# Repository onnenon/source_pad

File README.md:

# Source Pad

The Source Allies logo looks too similar to a 3x3 macropad to not make it into one...

## Case

## Source Code

## PCB

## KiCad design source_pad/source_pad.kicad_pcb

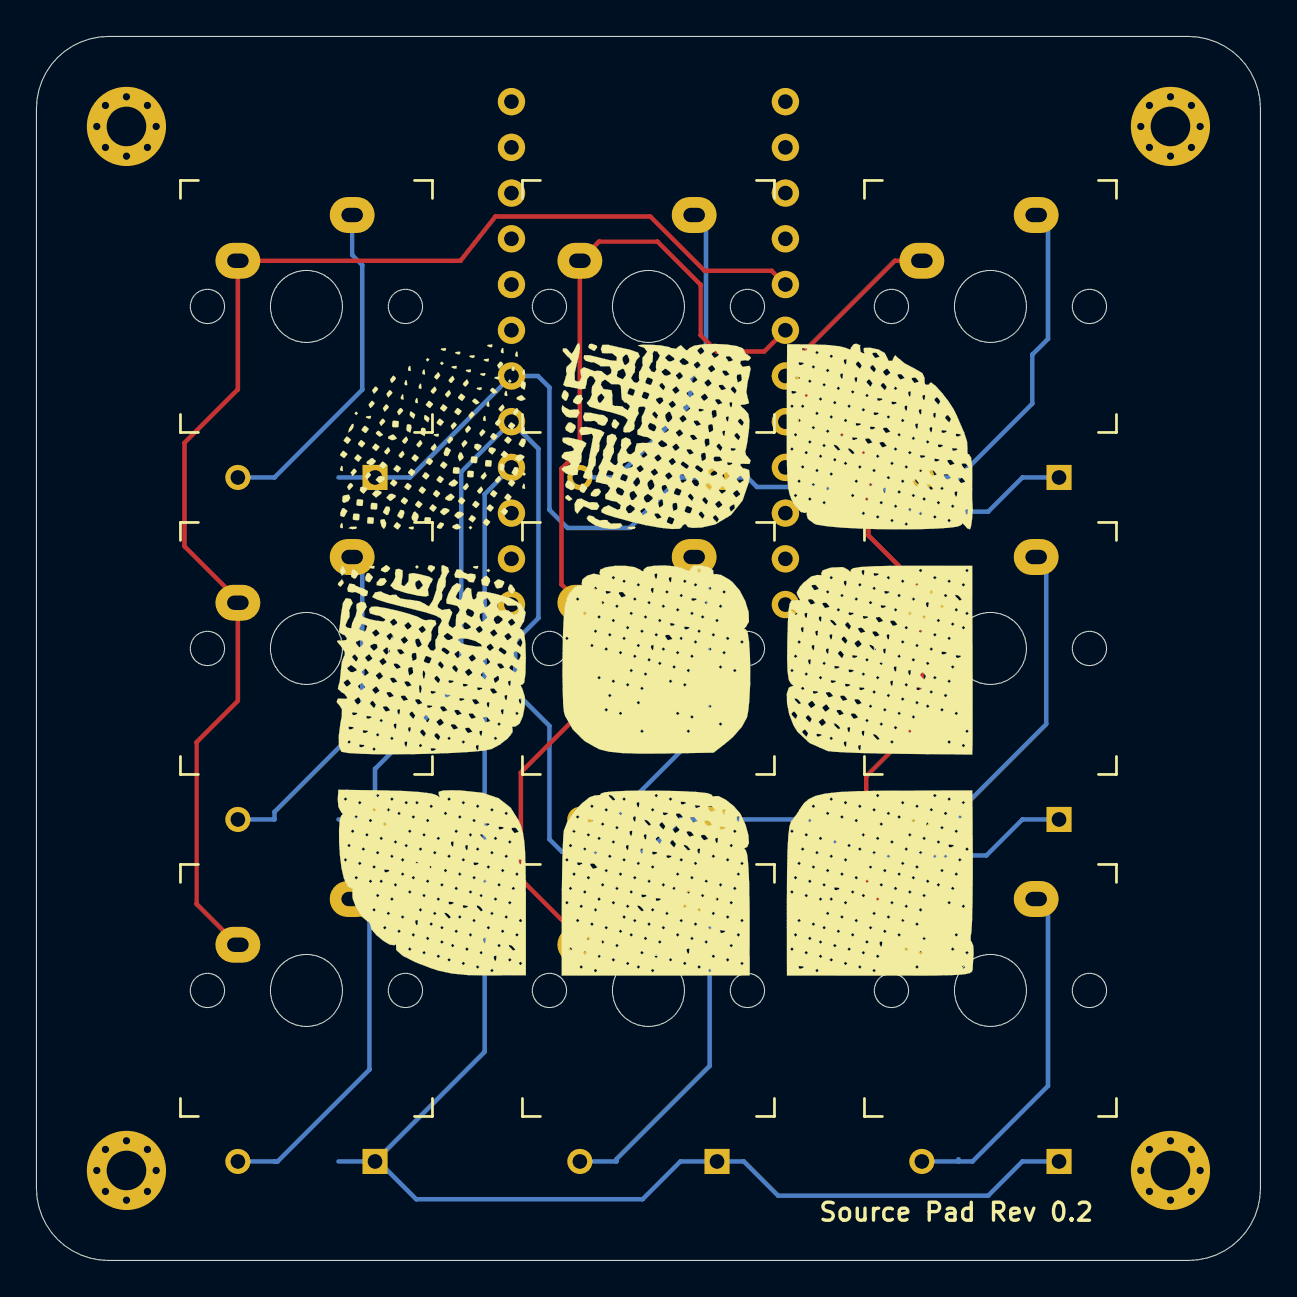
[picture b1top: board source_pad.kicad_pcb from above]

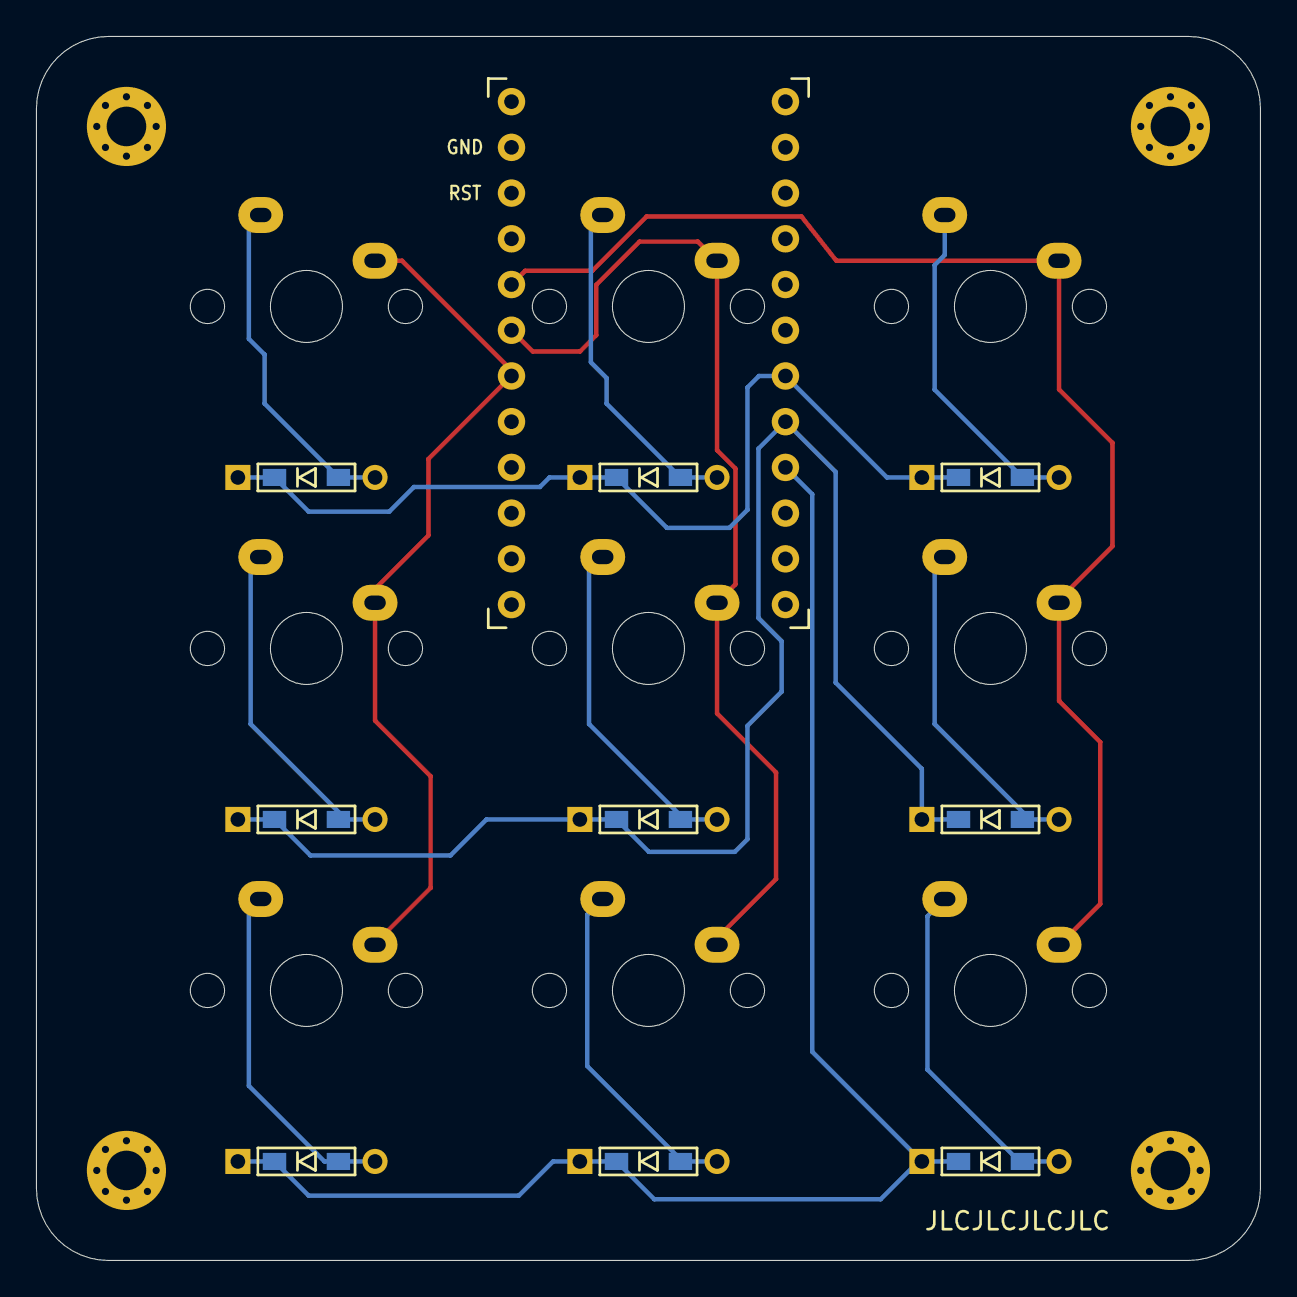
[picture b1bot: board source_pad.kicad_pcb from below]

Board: 2 copper layers, 68.0 x 68.0 mm, 19 parts (10 on the bottom side), 15 nets.

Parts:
D1, D2, D3, D4, D5, D6, D7, D8, D9: 1N4148W; D3_TH_SMD_SINGLE_SIDE
SW1, SW2, SW3, SW4, SW5, SW6, SW7, SW8, SW9: SW_PUSH; CherryMX_1u
U1: ProMicro-kbd; ProMicro_v3.5_fix

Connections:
unnamed: D1.2, SW1.2
unnamed: D2.2, SW2.2
unnamed: D3.2, SW3.2
unnamed: D4.2, SW4.2
unnamed: D5.2, SW5.2
unnamed: D6.2, SW6.2
unnamed: D7.2, SW7.2
unnamed: D8.2, SW8.2
unnamed: D9.2, SW9.2
col0: SW1.1, SW2.1, SW3.1, U1.20
col1: SW4.1, SW5.1, SW6.1, U1.19
col2: SW7.1, SW8.1, SW9.1, U1.18
row0: D1.1, D4.1, D7.1, U1.7
row1: D2.1, D5.1, D8.1, U1.8
row2: D3.1, D6.1, D9.1, U1.9

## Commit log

2020-07-10 Updated clearances
2020-07-10 Updated column traces
2020-07-10 Updated project structure
2020-07-10 Added makefile
2020-07-10 fixed mx pads
2020-07-10 Create LICENSE
2020-07-10 Added plate file
2021-02-06 Added images, case file
2021-02-06 Added case images
